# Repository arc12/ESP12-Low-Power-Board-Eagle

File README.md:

# ESP12 Low Power Board
Repo for a PCB based around the ESP12 module intended to support low power use with deep sleep and 18650 cell. It is designed to allow multiple options, outlined below.

## Configuration
Solder jumpers are intended for settings which are constant for a given application of the board, e.g. an X sensor attached. Normal jumpers are for settings which might vary between locations or at different times (including setup and testing).

__SJ1__ (Deep Sleep) - Option A routes GPIO16 to the breakout for normal IO use; option B connects it to the reset pin for use of Deep Sleep.  
__SJ2,3__ - These jumpers are NC and may be cut if the serial adapter does not have both DTR and RTS signals on the relevant pins. If these signals are present, then flashing (and terminal reset) will be automatic. Otherwise S1 and S2 must be used. Note that if DTR is connected (and the Serial adapter is powered via either the battery connection or USB) then the “Cmd” (aka Flash) button cannot be used as an input. RTS may be connected and DTR left unconnected; in this case S1 must be used when boot-loading firmware, with only the reset function being automatic (pressing S2 not needed).  
__JP1-3__ (Cfg0/1/2) - May be used to select runtime configurations, for example to put the software into a testing or calibration loop. Omit these if the GPIOs will be used at the Breakout header. GPIO14 can either be programmed as Cfg2 or used for peripheral power control (p-Vcc, see below): pin pair “A” is for Cfg2 and “B” is for enabling the p-Vcc control.  
__JP4,5__ (Signal) - If shorted, LEDs 1 and 2 are connected to GPIO2 or GPIO0, respectively. This is intended for testing. May be omitted, along with the LEDs and resistors. GPIO2 shows activity during flashing and boot.  
__JP6__ (USB Power) - If shorted, allows for the USB-Serial breakout to power the device. NB: must be 3.3V regulated. In this case, the battery should be disconnected (although this is probably not critical). Normally open (or no header).  
__JP7__ (LDO Enable) - allows the LDO enable to be controlled off-board. Cut the PCB track jumper on the underside to use this.
__JP8__ (Diode Bypass) - allows the reverse supply protection schottky diode to be bypassed. Normally leave unpopulated.  
__JP9__ (Permanent Peripheral VCC) - See below.

## Runtime Switches
__S1__ (Flash/Cmd) -  Reset will trigger the boot loader if this switch is held on (i.e. flashing is done by holding S1 and then pressing/releasing S2). Once the new programme has been flashed, S2 (reset) must be done manually. After boot, this may be used as an ad hoc “command” (if DTR is not connected). This is active low.  
__S2__ (Reset) - ESP-12 reset.

## Headers
### Serial
UART pins and power, intended for flashing the device and diagnostic monitoring, although some applications might use them. When using a Bluetooth serial monitor, JP6 should be on, to supply it with power. Note that the pin labels are to match those on the serial device, rather than being those of the ESP8622.  See note on JP6. 3.3V logic must be used.

Note that, if the DTR and RTS signals are connected, then the PlatformIO monitor (or any other serial interaction which is not bootloading) must be configured as follows (add to platformio.ini), otherwise attempts to use the Monitor cause the board to hang (recovers if the monitor is killed):
```
monitor_rts = 0
monitor_dtr = 0
```

### Breakout
ESP-12 I/O and power for attached devices. The higher pin numbers may also be used for on board functions, in which case a shorter set of header pins can be used.

Some notes:
- GPIO 4 and 5 may be used without consideration, and are conventionally used for I2C.
- A0 may be used only if battery monitoring is NOT being used.
- GPIO 12 and 13 may be used at the breakout or one/both may be used for configuration setting.
- GPIO 14 may be used for onboard signalling for testing via JP4, for control of power to "peripherals" (see below), or used for I/O at the breakout header.
- GPIO 16 is used for sleep control in Deep Sleep (active low, drives RST). Avoid using at the breakout if deep sleep is used (this GPIO has other limitations too: see datasheet).
- RST can be used to wake the ESP8266 from a deep sleep.

### I2C
Convenience headers, ordered to match the SHT4X, BH1750, ... breakout boards. Note that one has the power pins reversed.

## Omittable Components
- LEDs and related resistors and jumpers.
- JP1-3 and headers.
- R10,11 should be omitted if I2C communications is not occurring on GPIO4,5. A value of 4k7 is shown but values between 10k and 2.2k are normal. Some breakout boards already include 10k pull-up resistors, which may be satisfactory; if so, omit R10,11, especially if there is more than one I2C breakout with pull-ups present.
- Q1, R12, JP8, JP3 (partial) - see next section.
- JP7, if PCB trace not cut.
- S1 is usually not needed.
- S3, S4 - see next section.
- EP2, EP3 - see next section.
- D1, JP8, JP7, C1, C2, U2 - if powering through E2, see next section.

The ESP-12 modules have a LED on GPIO2, which may be unwanted!

## Optional Extras

### External Power
The main use case is to use the on-board 18650 battery clip, with the clip wires soldered to EP1. Alternatively, an off-board battery may be connected using a screw terminal or solderless connector at EP1.

Alternatives are:  
- use EP2 to connect a 3.3V PSU, in which case the voltage regulation components through to U2 should be omitted.  
- use EP3, a USB-mini socket to supply 5V

### Reed Switches
Provision is made to place two reed switches on the underside so that sealed enclosures can be crudely controlled from the outside using magnets with N-S pole alignments parallel to the reed switch axes. One switch (S3) is parallel with Cfg1 and another (S4) parallel to the Reset switch. A typical use is to use Cfg1 to set the device into OTA update & web server mode, then resetting to wake from sleep.

### Peripheral/sensor Power Rail Control Option
__AKA p-Vcc__
This option allows the ESP8266 to disconnect power to the peripherals on SV2-5. NB: SV1 is not affected since power may be supplied TO the board via that header.

The default case is Vcc to peripherals being “permanent”; Q1 + R12 should be omitted (and JP3 reduced to 2 pins). If p-Vcc is required then cut the PCB track on the under-side of JP9. The normal operating condition will have JP9 open and JP3 set to connect GPIO14 to Q1 (option B on PCB silk). In this case, Cfg2 cannot be used. The MCU will need to restore power by pulling GPIO14 low before attempting communications. JP9 maybe closed to override the control to “always on”.

JP3 may be soldered as a 2 pin or 3 pin configuration according to need, for example to allow for the situation when R12 and Q1 are in place but no longer used; i.e. it allows GPIO14 to be used without R12 acting as a pull-up. In this case, JP9 would be closed.

## Future Variant Ideas
To allow for 5V devices (even if 3.3V logic): a double LiPo battery with both 5V and 3.3V step-down and mosfet power rail control.

## Device Construction Notes
_To match software, elsewhere in a currently-private repo._
### TH
Options:
- Remove LED from ESP-12
- Battery and LDO circuit as normal, omit JP8 and the PSU connector. (track under JP7 intact)
- Omit p-Vcc components (track under JP9 intact)
- LED2 as amber, 180R resistor, with jumper. (omit LED1 and R9)
- Cfg0 and Cfg1 jumpers (neither connected for normal use.
- SJ3 to deep sleep.
- Include serial header and external power jumper, but no others; solder SHT40 direct to one I2C header slot.
- Reset switch but not "flash/cmd" (omit R7).

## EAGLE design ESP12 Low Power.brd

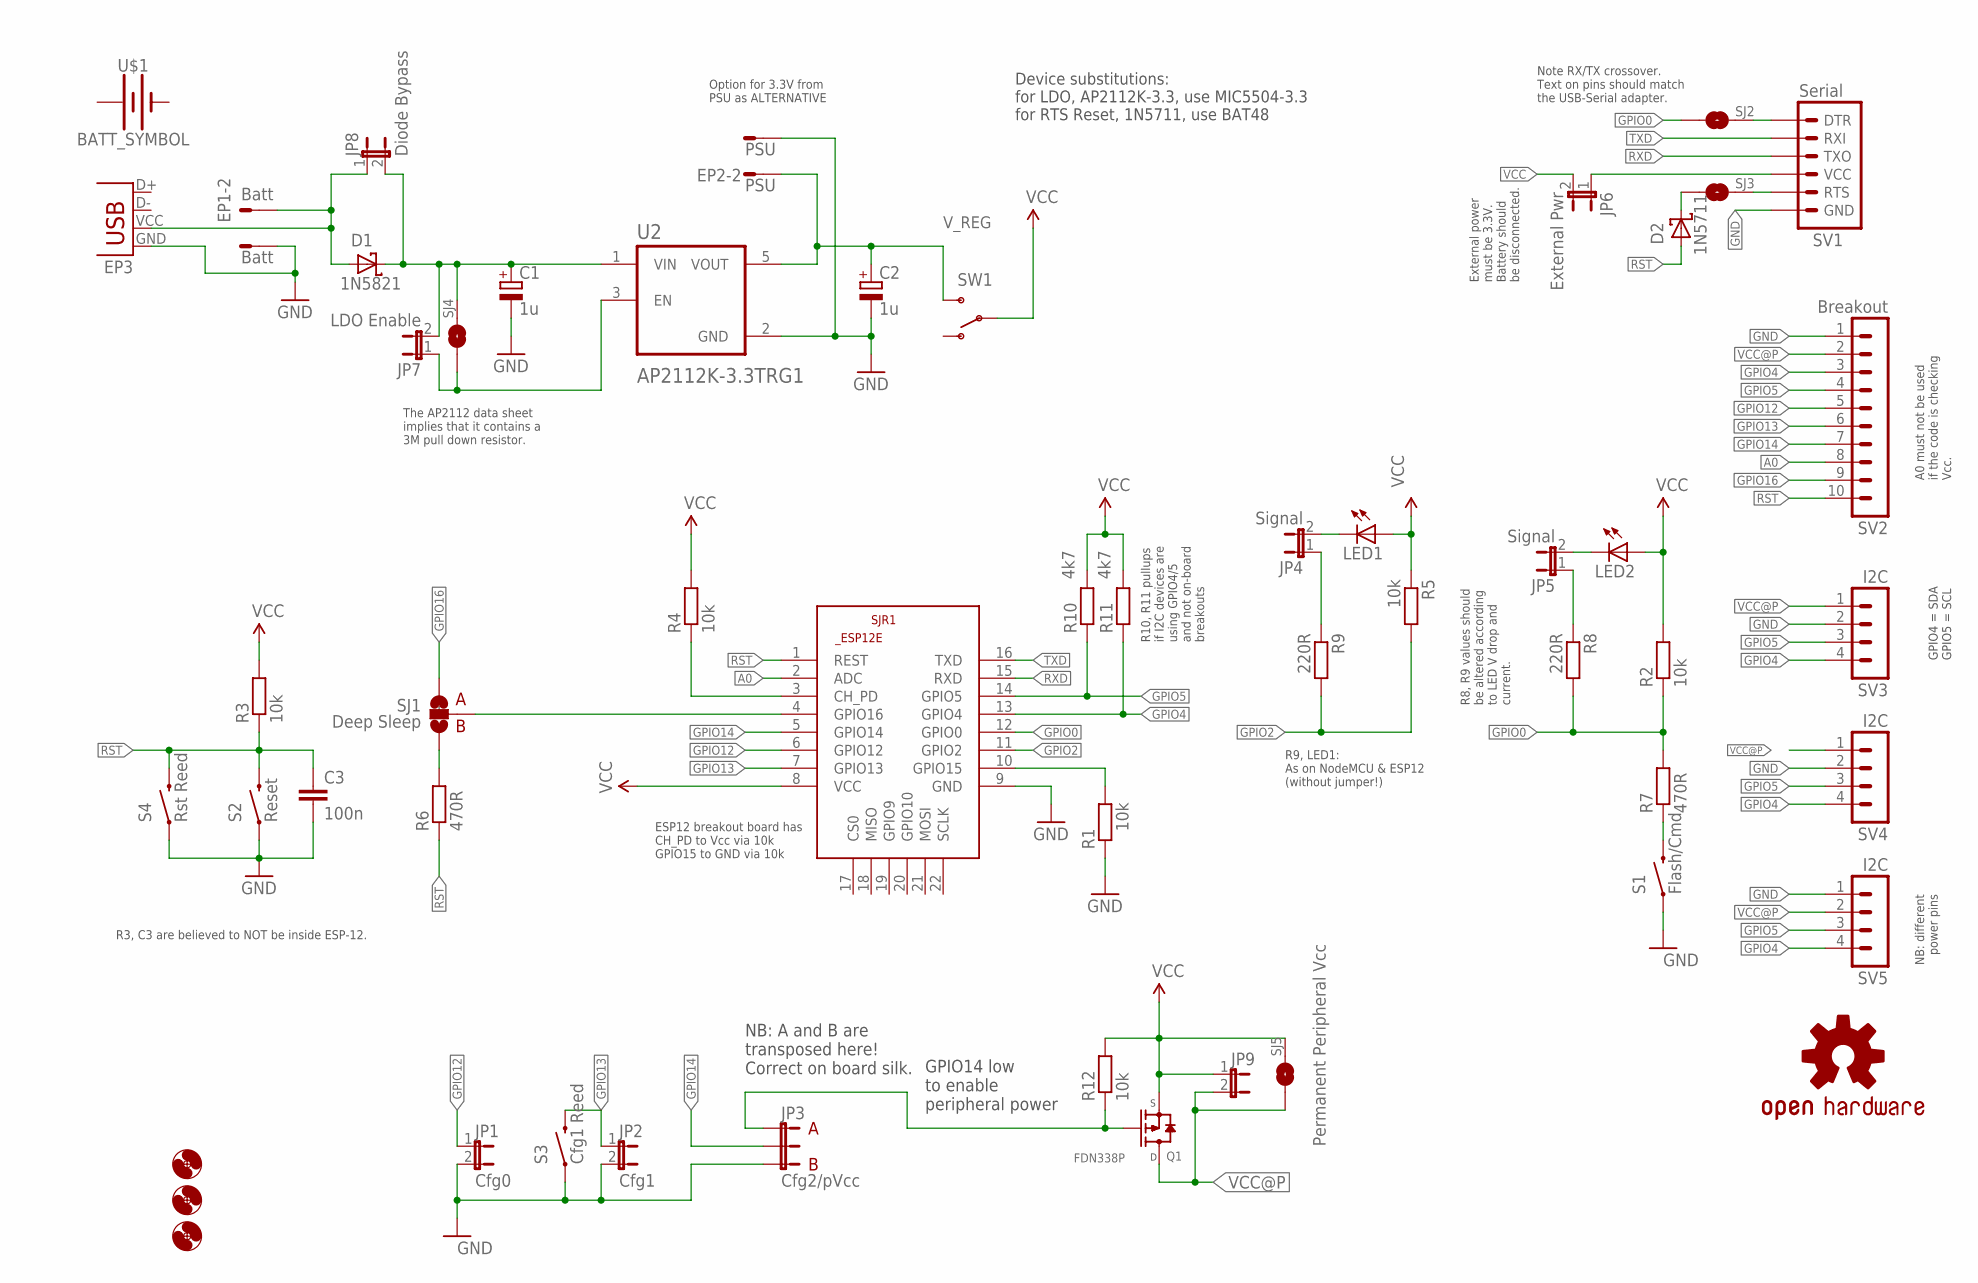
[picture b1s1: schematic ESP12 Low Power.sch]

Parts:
C1, C2: 1u; E2,5-5
C3: 100n; 1206
D1: 1N5821; DO201-15
D2: 1N5711; DO35-7
EP1: Batt; 02P
EP2: PSU; 02P
EP3: USB-FCI_SMD***; FCI_USB_B_SMD
H1, H2, H4: MOUNT-HOLE3.2; 3,2
JP1: Cfg0; 1X02
JP2: Cfg1; 1X02
JP3: Cfg2/pVcc; 1X03_JMP
JP4, JP5: Signal; 1X02
JP6: External Pwr; 1X02
JP7: LDO Enable; 1X02
JP8: Diode Bypass; 1X02
JP9: Permanent Peripheral Vcc; 1X02
LED1, LED2: LED1206; LED-1206
LOGO1: OSHW-LOGOM; OSHW-LOGO-M
Q1: FDN338P; SOT23
R1, R2, R3, R4, R5: 10k; 1206
R6, R7: 470R; 0204/7
R8, R9: 220R; 0204/7
R10, R11: 4k7; 1206
R12: 10k; 0204/7
S1: Flash/Cmd; TACTILE-PTH
S2: Reset; TACTILE-PTH
S3: Cfg1 Reed; REED_SWITCH_PTH
S4: Rst Reed; REED_SWITCH_PTH
SJ1: Deep Sleep; SJ_3
SJ2, SJ3, SJ4, SJ5: SOLDERJUMPERTRACE; SJ_2S-TRACE
SJR1: ESP8266-12EESP12E; ESP8266-ESP12E
SV1: Serial; 1X06-KIT
SV2: Breakout; MA10-1
SV3, SV4, SV5: I2C; MA04-1
SW1: SWITCH_SPDTMULTICOMP_MS2; MULTICOMP_2MS
U2: AP2112K-3.3TRG1; SOT95P285X140-5N
U$1: BATT_SYMBOL; BATTERY_18650-HOLDER_SILK

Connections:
A0: SJR1.2 (ADC), SV2.8
GND: C1.-, C2.-, C3.2, EP1.2, EP2.1, EP3.GND, JP1.2, JP2.2, JP3.3, R1.1, S1.1, S2.1, S3.P$1 (1), S4.P$1 (1), SJR1.9 (GND), SV1.1 (GND), SV2.1, SV3.2, SV4.2, SV5.1, U2.2 (GND)
GPIO0: R2.1, R7.2, R8.2, SJ2.1, SJR1.12 (GPIO0)
GPIO2: R5.2, R9.2, SJR1.11 (GPIO2)
GPIO4: R11.1, SJR1.13 (GPIO4), SV2.3, SV3.4, SV4.4, SV5.4
GPIO5: R10.1, SJR1.14 (GPIO5), SV2.4, SV3.3, SV4.3, SV5.3
GPIO12: JP1.1, SJR1.6 (GPIO12), SV2.5
GPIO13: JP2.1, S3.P$2 (2), SJR1.7 (GPIO13), SV2.6
GPIO14: JP3.2, SJR1.5 (GPIO14), SV2.7
GPIO16: SJ1.1, SV2.9
unnamed: R7.1, S1.3 (2)
unnamed: R1.2, SJR1.10 (GPIO15)
unnamed: JP7.1, SJ4.1, U2.3 (EN)
unnamed: JP4.2, LED1.C
unnamed: SJ3.2, SV1.2 (RTS)
unnamed: JP4.1, R9.1
unnamed: JP5.2, LED2.C
unnamed: C1.+, D1.C, JP7.2, JP8.2, SJ4.2, U2.1 (VIN)
unnamed: JP6.1, SV1.3 (VCC)
unnamed: SJ2.2, SV1.6 (DTR)
unnamed: R6.2, SJ1.3
unnamed: SJ1.2, SJR1.4 (GPIO16)
unnamed: D1.A, EP1.1, EP3.VCC (VBUS), JP8.1
unnamed: D2.C, SJ3.1
unnamed: JP5.1, R8.1
unnamed: R4.1, SJR1.3 (CH_PD)
unnamed: JP3.1, Q1.1 (G), R12.1
RST: C3.1, D2.A, R3.1, R6.1, S2.3 (2), S4.P$2 (2), SJR1.1 (REST), SV2.10
RXD: SJR1.15 (RXD), SV1.4 (TXO)
TXD: SJR1.16 (TXD), SV1.5 (RXI)
VCC: JP6.2, JP9.1, LED1.A, LED2.A, Q1.2 (S), R2.2, R3.2, R4.2, R5.1, R10.2, R11.2, R12.2, SJ5.2, SJR1.8 (VCC), SW1.P$2
VCC@P: JP9.2, Q1.3 (D), SJ5.1, SV2.2, SV3.1, SV4.1, SV5.2
V_REG: C2.+, EP2.2, SW1.P$3 (S), U2.5 (VOUT)

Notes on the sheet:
R3, C3 are believed to NOT be inside ESP-12.
R9, LED1: As on NodeMCU & ESP12 (without jumper!)
A0 must not be used if the code is checking Vcc.
ESP12 breakout board has CH_PD to Vcc via 10k GPIO15 to GND via 10k
GPIO4 = SDA GPIO5 = SCL
The AP2112 data sheet implies that it contains a 3M pull down resistor.
Note RX/TX crossover. Text on pins should match the USB-Serial adapter.
R10, R11 pullups if I2C devices are using GPIO4/5 and not on-board breakouts
External power must be 3.3V. Battery should be disconnected.
R8, R9 values should be altered according to LED V drop and current.
GPIO14 low to enable peripheral power
Option for 3.3V from PSU as ALTERNATIVE
NB: different power pins
NB: A and B are transposed here! Correct on board silk.
Device substitutions: for LDO, AP2112K-3.3, use MIC5504-3.3 for RTS Reset, 1N5711, use BAT48

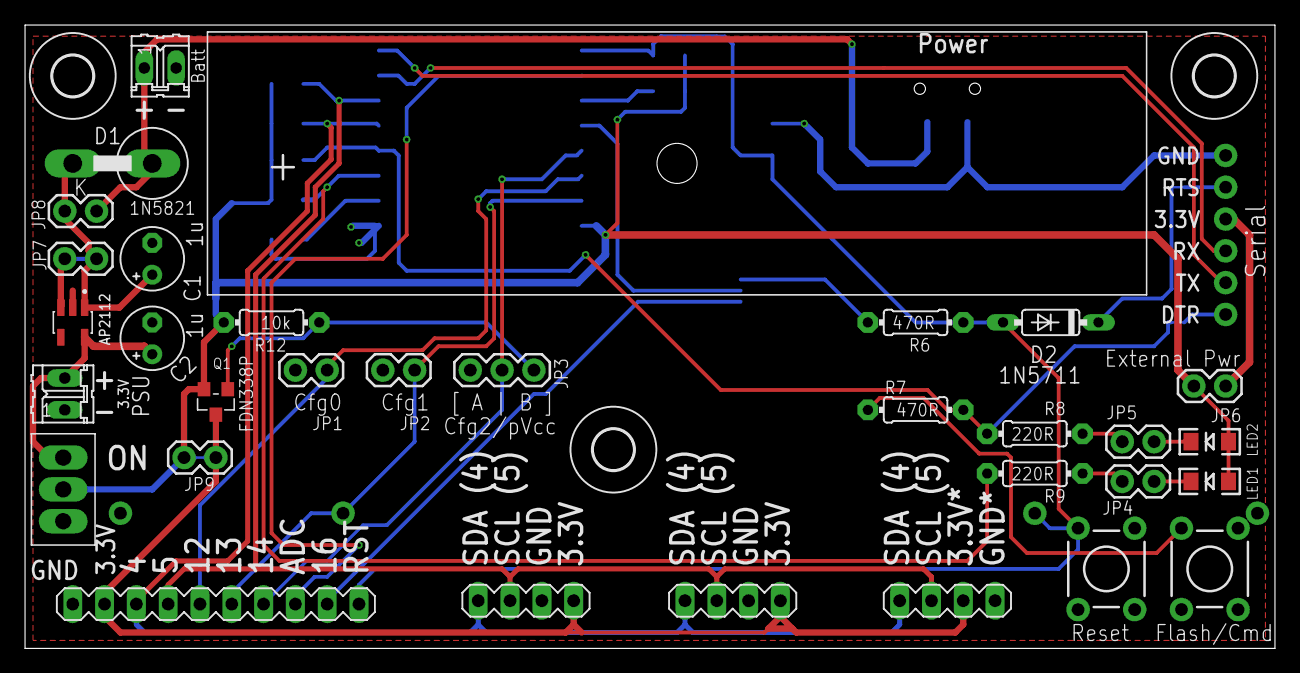
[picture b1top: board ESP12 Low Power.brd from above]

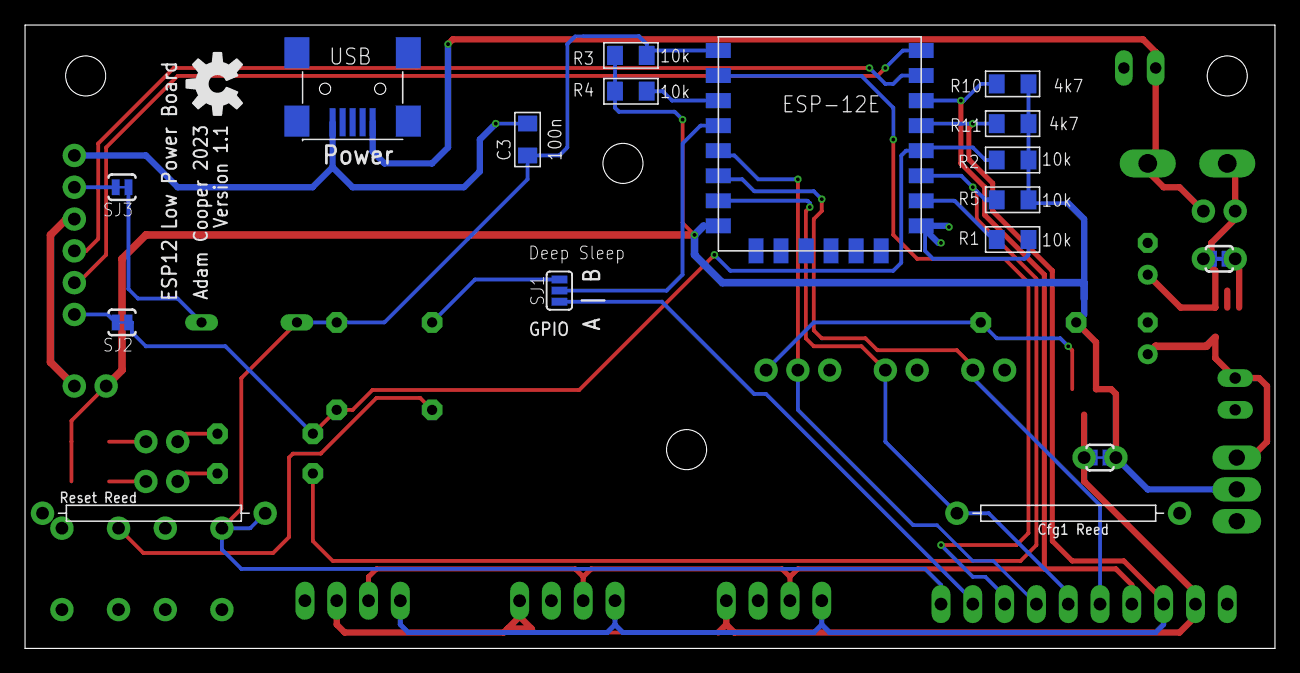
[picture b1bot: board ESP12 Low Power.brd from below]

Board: 2 copper layers, 99.8 x 49.8 mm, 54 parts (18 on the bottom side), 33 nets.

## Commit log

2023-06-21 Initial commit of v1.0. Probably complete and OK but not yet "released".
2023-06-21 move some things away from screw holes on board
2023-06-21 Add configuration and use notes to ReadMe
2023-06-21 md format error
2023-07-10 Fixes and clarifications to README + some changes to schematic annotations (no circuit change)
2023-07-26 clarifications and formatting of readme
2023-11-23 Changes for v1.1 See Github issues

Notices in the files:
parts and their libraries:
SparkFun-Passives: Licensing: CC v3.0 Share-Alike You are welcome to use this library for commercial purposes.
SparkFun-Aesthetics: Licensing: Creative Commons ShareAlike 4.0 International - https://creativecommons.org/licenses/by-sa/4.0
